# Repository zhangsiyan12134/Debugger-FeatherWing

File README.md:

# Debugger-FeatherWing
A I/O indicator module for Adafruit Feather Platform.

Uses 74HVC541 buffer chip to drive the LEDs

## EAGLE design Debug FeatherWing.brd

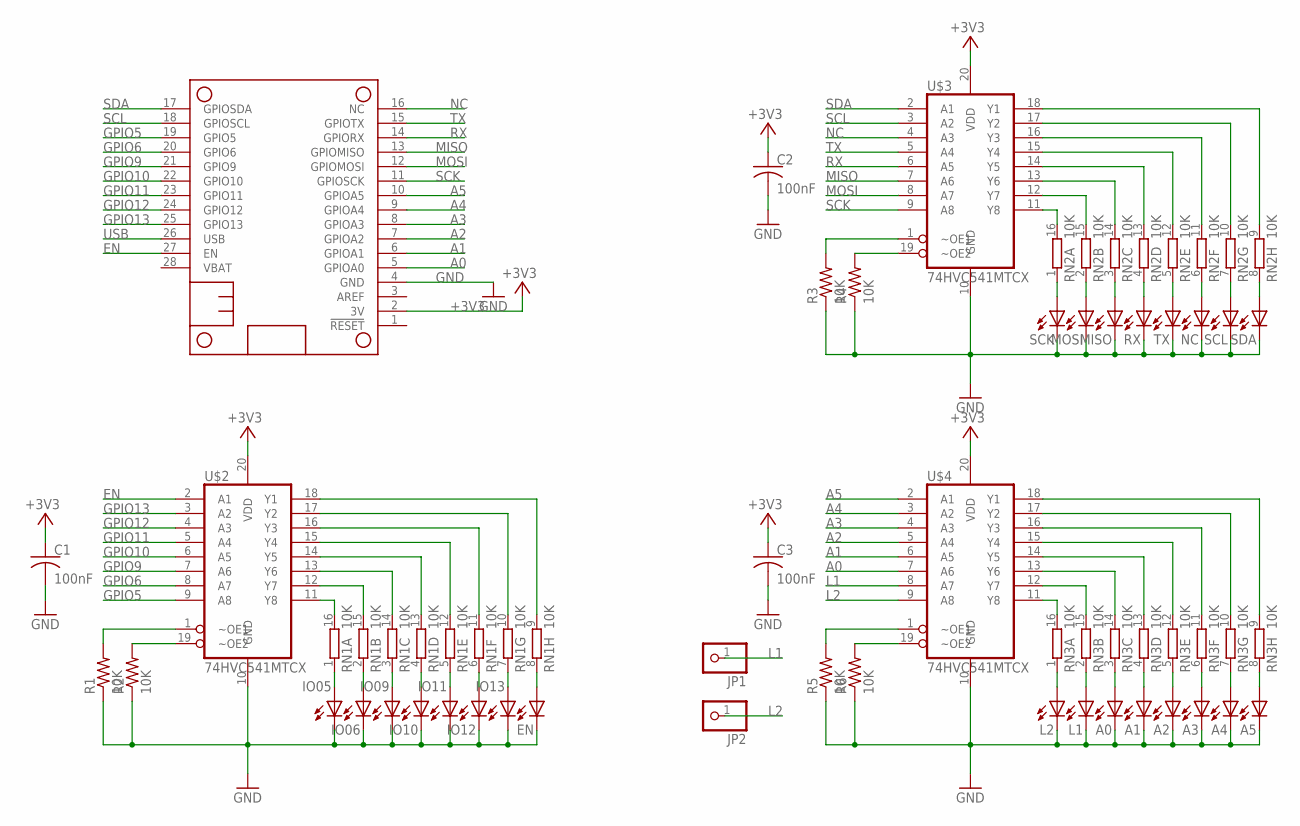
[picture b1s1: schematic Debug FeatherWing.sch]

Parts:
A0, A1, A2, A3, A4, A5: Green; CHIPLED_0805
C1, C2, C3: 100nF; C0805
EN: Green; CHIPLED_0805
IO05, IO06, IO09, IO10, IO11, IO12, IO13: Green; CHIPLED_0805
JP1, JP2: PINHD-1X1; 1X01
L1, L2: Green; CHIPLED_0805
MISO: Green; CHIPLED_0805
MOSI: Green; CHIPLED_0805
MS1: FEATHERWING
NC: Green; CHIPLED_0805
R1, R2, R3, R4, R5, R6: 10K; R0805
RN1, RN2, RN3: 10K; EXB2HV
RX: Green; CHIPLED_0805
SCK: Green; CHIPLED_0805
SCL: Green; CHIPLED_0805
SDA: Green; CHIPLED_0805
TX: Green; CHIPLED_0805
U$2, U$3, U$4: 74HVC541MTCX; TSSOP20

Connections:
+3V3: C1.1, C2.1, C3.1, MS1.2 (3V), U$2.20 (VDD), U$3.20 (VDD), U$4.20 (VDD)
A0: MS1.5 (GPIOA0), U$4.7 (A6)
A1: MS1.6 (GPIOA1), U$4.6 (A5)
A2: MS1.7 (GPIOA2), U$4.5 (A4)
A3: MS1.8 (GPIOA3), U$4.4 (A3)
A4: MS1.9 (GPIOA4), U$4.3 (A2)
A5: MS1.10 (GPIOA5), U$4.2 (A1)
EN: MS1.27 (EN), U$2.2 (A1)
GND: A0.C, A1.C, A2.C, A3.C, A4.C, A5.C, C1.2, C2.2, C3.2, EN.C, IO05.C, IO06.C, IO09.C, IO10.C, IO11.C, IO12.C, IO13.C, L1.C, L2.C, MISO.C, MOSI.C, MS1.4 (GND), NC.C, R1.1, R2.1, R3.1, R4.1, R5.1, R6.1, RX.C, SCK.C, SCL.C, SDA.C, TX.C, U$2.10 (GND), U$3.10 (GND), U$4.10 (GND)
GPIO5: MS1.19 (GPIO5), U$2.9 (A8)
GPIO6: MS1.20 (GPIO6), U$2.8 (A7)
GPIO9: MS1.21 (GPIO9), U$2.7 (A6)
GPIO10: MS1.22 (GPIO10), U$2.6 (A5)
GPIO11: MS1.23 (GPIO11), U$2.5 (A4)
GPIO12: MS1.24 (GPIO12), U$2.4 (A3)
GPIO13: MS1.25 (GPIO13), U$2.3 (A2)
L1: JP1.1, U$4.8 (A7)
L2: JP2.1, U$4.9 (A8)
MISO: MS1.13 (GPIOMISO), U$3.7 (A6)
MOSI: MS1.12 (GPIOMOSI), U$3.8 (A7)
unnamed: RN1.9 (2), U$2.18 (Y1)
unnamed: RN1.10 (2), U$2.17 (Y2)
unnamed: RN1.11 (2), U$2.16 (Y3)
unnamed: RN1.12 (2), U$2.15 (Y4)
unnamed: RN1.13 (2), U$2.14 (Y5)
unnamed: RN1.14 (2), U$2.13 (Y6)
unnamed: RN1.15 (2), U$2.12 (Y7)
unnamed: RN1.16 (2), U$2.11 (Y8)
unnamed: IO05.A, RN1.1
unnamed: IO06.A, RN1.2 (1)
unnamed: IO09.A, RN1.3 (1)
unnamed: IO10.A, RN1.4 (1)
unnamed: IO11.A, RN1.5 (1)
unnamed: IO12.A, RN1.6 (1)
unnamed: IO13.A, RN1.7 (1)
unnamed: EN.A, RN1.8 (1)
unnamed: R3.2, U$3.1 (~OE1)
unnamed: R4.2, U$3.19 (~OE2)
unnamed: RN2.9 (2), U$3.18 (Y1)
unnamed: RN2.10 (2), U$3.17 (Y2)
unnamed: RN2.11 (2), U$3.16 (Y3)
unnamed: RN2.12 (2), U$3.15 (Y4)
unnamed: RN2.13 (2), U$3.14 (Y5)
unnamed: RN2.14 (2), U$3.13 (Y6)
unnamed: RN2.15 (2), U$3.12 (Y7)
unnamed: RN2.16 (2), U$3.11 (Y8)
unnamed: RN2.1, SCK.A
unnamed: MOSI.A, RN2.2 (1)
unnamed: MISO.A, RN2.3 (1)
unnamed: RN2.4 (1), RX.A
unnamed: RN2.5 (1), TX.A
unnamed: NC.A, RN2.6 (1)
unnamed: R1.2, U$2.1 (~OE1)
unnamed: R2.2, U$2.19 (~OE2)
unnamed: RN2.7 (1), SCL.A
unnamed: RN2.8 (1), SDA.A
unnamed: R5.2, U$4.1 (~OE1)
unnamed: R6.2, U$4.19 (~OE2)
unnamed: RN3.9 (2), U$4.18 (Y1)
unnamed: RN3.10 (2), U$4.17 (Y2)
unnamed: RN3.11 (2), U$4.16 (Y3)
unnamed: RN3.12 (2), U$4.15 (Y4)
unnamed: RN3.13 (2), U$4.14 (Y5)
unnamed: RN3.14 (2), U$4.13 (Y6)
unnamed: RN3.15 (2), U$4.12 (Y7)
unnamed: RN3.16 (2), U$4.11 (Y8)
unnamed: L2.A, RN3.1
unnamed: L1.A, RN3.2 (1)
unnamed: A0.A, RN3.3 (1)
unnamed: A1.A, RN3.4 (1)
unnamed: A2.A, RN3.5 (1)
unnamed: A3.A, RN3.6 (1)
unnamed: A4.A, RN3.7 (1)
unnamed: A5.A, RN3.8 (1)
NC: MS1.16 (NC), U$3.4 (A3)
RX: MS1.14 (GPIORX), U$3.6 (A5)
SCK: MS1.11 (GPIOSCK), U$3.9 (A8)
SCL: MS1.18 (GPIOSCL), U$3.3 (A2)
SDA: MS1.17 (GPIOSDA), U$3.2 (A1)
TX: MS1.15 (GPIOTX), U$3.5 (A4)
USB: MS1.26 (USB)

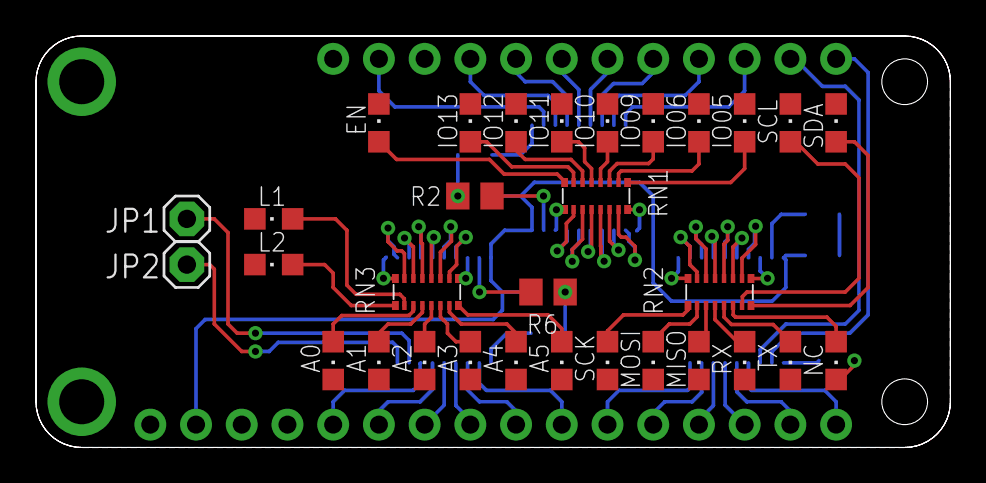
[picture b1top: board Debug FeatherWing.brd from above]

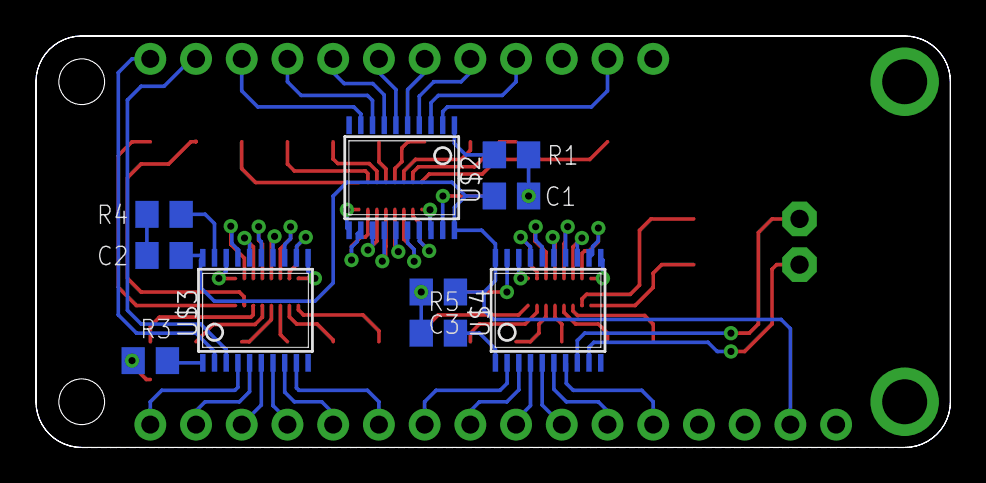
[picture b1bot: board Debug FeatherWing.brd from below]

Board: 2 copper layers, 50.8 x 22.9 mm, 42 parts (10 on the bottom side), 80 nets.

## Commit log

2022-07-10 Initial Commit
    Initial Commit
2022-07-10 Image for README
    Image for README
